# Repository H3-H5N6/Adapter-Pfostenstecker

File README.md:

# Beschreibung

Adapterplatine, um einen 2x8-poligen Pfostenstecker mit einem Steckbrett benutzt werden kann.

# Changelog

## v1.0

* Initial

# Schaltplan

# Bestückungsplan

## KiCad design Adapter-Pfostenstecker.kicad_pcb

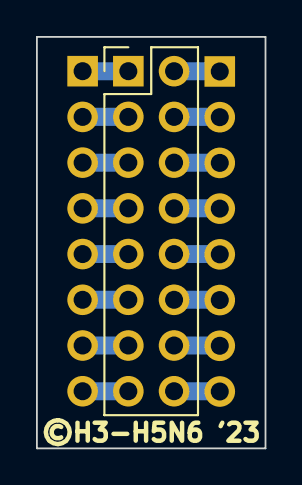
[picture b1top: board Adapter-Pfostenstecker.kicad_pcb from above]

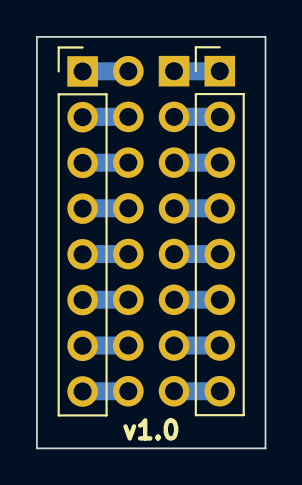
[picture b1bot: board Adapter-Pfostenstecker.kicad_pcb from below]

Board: 2 copper layers, 12.7 x 22.9 mm, 3 parts (2 on the bottom side), 16 nets.

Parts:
J1001: Conn_02x08_Odd_Even; PinHeader_2x08_P2.54mm_Vertical
J1002, J1003: Conn_01x08; PinHeader_1x08_P2.54mm_Vertical

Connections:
unnamed: J1001.1, J1003.1
unnamed: J1001.2, J1002.1
unnamed: J1001.3, J1003.2
unnamed: J1001.4, J1002.2
unnamed: J1001.5, J1003.3
unnamed: J1001.6, J1002.3
unnamed: J1001.7, J1003.4
unnamed: J1001.8, J1002.4
unnamed: J1001.9, J1003.5
unnamed: J1001.10, J1002.5
unnamed: J1001.11, J1003.6
unnamed: J1001.12, J1002.6
unnamed: J1001.13, J1003.7
unnamed: J1001.14, J1002.7
unnamed: J1001.15, J1003.8
unnamed: J1001.16, J1002.8

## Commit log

2023-11-27 Initial
2023-11-27 Schaltplan auch als png erzeugen.
2023-11-27 schematic pdf wieder erzeugen
2023-11-27 Fix schematic svg

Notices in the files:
Adapter-Pfostenstecker.kicad_pcb:
©H3-H5N6 2021 CAN-Bus-Decoder v1.1
©H3-H5N6 '23
